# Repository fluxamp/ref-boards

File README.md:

## About

This repository contains the layout for two voltage reference boards intended as standalone devices and for integration with other modules.

Feel free to copy, modify and redistribute the schematic and layout.

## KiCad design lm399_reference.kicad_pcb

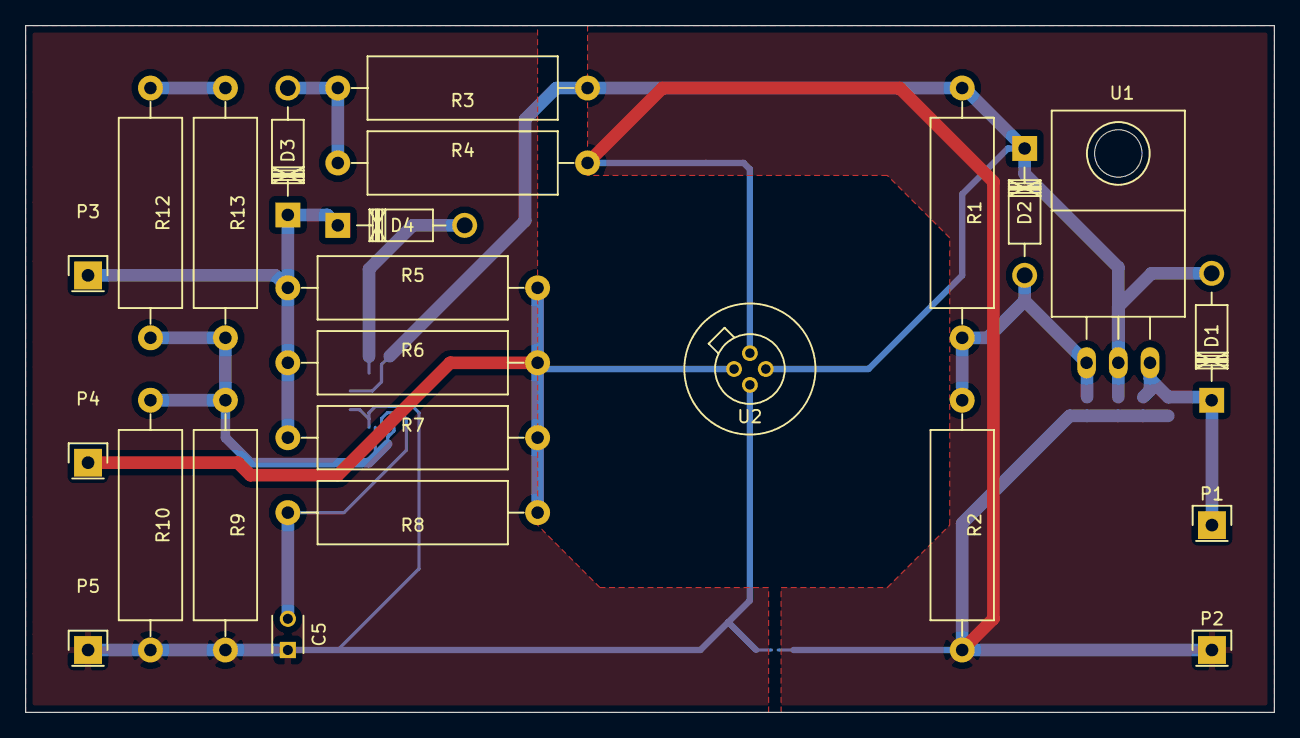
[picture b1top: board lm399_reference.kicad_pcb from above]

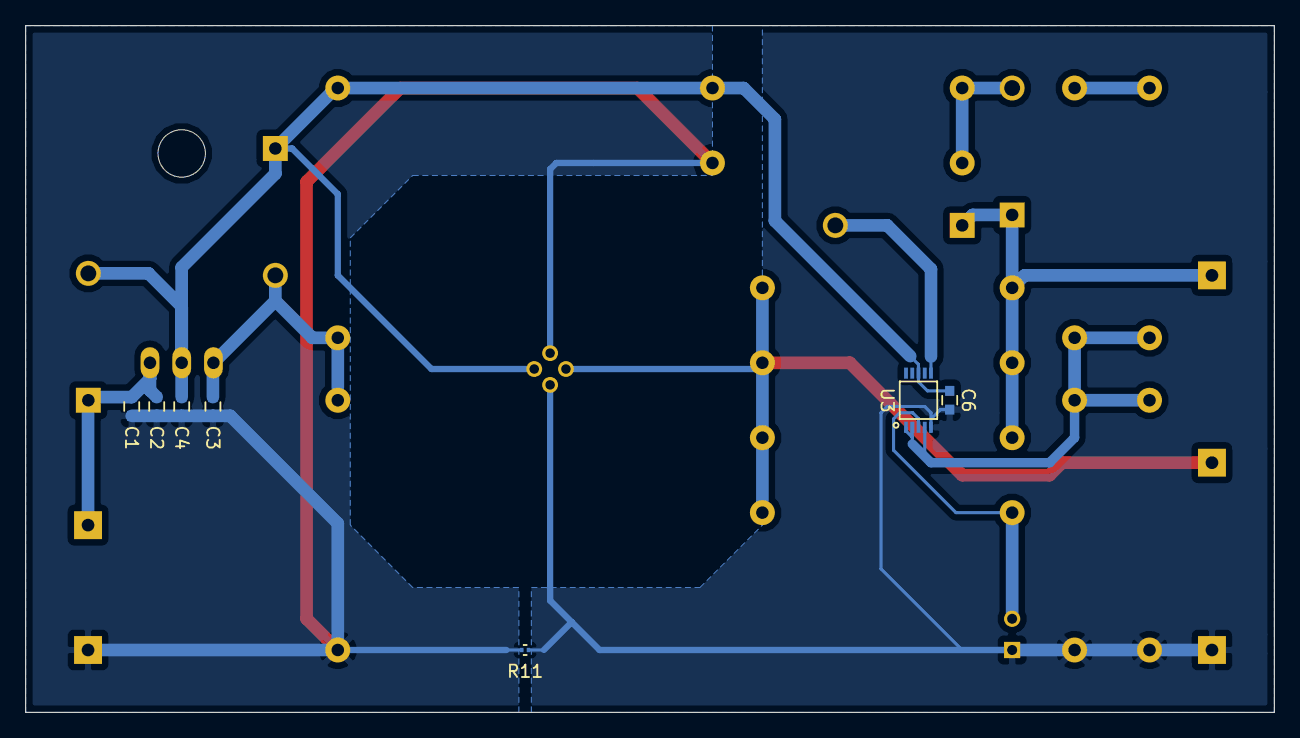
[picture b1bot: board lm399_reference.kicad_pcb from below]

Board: 2 copper layers, 100.0 x 55.0 mm, 31 parts (7 on the bottom side), 11 nets.

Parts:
C1, C3: 10u; C_0603
C2, C6: 100n; C_0603
C4: 1u; C_0603
C5: 100n; C_Disc_D3_P2.5
D1, D2: 1N4001; Diode_DO-41_SOD81_Horizontal_RM10
D3, D4: 1N4148; Diode_DO-41_SOD81_Horizontal_RM10
P1: VIN; Pin_Header_Straight_1x01
P2: GND; Pin_Header_Straight_1x01
P3: 10V; Pin_Header_Straight_1x01
P4: 7V; Pin_Header_Straight_1x01
P5: 10V_GND; Pin_Header_Straight_1x01
R1: 205R; Resistor_Horizontal_RM20mm
R2: 2k26; Resistor_Horizontal_RM20mm
R3, R9: 20k; Resistor_Horizontal_RM20mm
R4: 5k; Resistor_Horizontal_RM20mm
R5, R6, R7, R12, R13: 10k; Resistor_Horizontal_RM20mm
R8: 550R; Resistor_Horizontal_RM20mm
R10: 24k9; Resistor_Horizontal_RM20mm
R11: 0R; C_0201
U1: LM317T; TO-220
U2: LM399
U3: LTC2057-MS10; MSOP-10

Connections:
7V: P4.1, R5.2, R6.2, R7.2, R8.1, U2.1
+15V: C4.1, C6.1, D1.2, D2.1, R1.1, R3.1, U1.2, U2.3, U3.8
GND: C1.2, C2.2, C3.2, C4.2, P2.1, R2.2, R4.2, R11.2, U2.4
GNDA: C5.1, C6.2, P5.1, R9.2, R10.2, R11.1, U2.2, U3.5
unnamed: C3.1, D2.2, R1.2, R2.1, U1.1
unnamed: C5.2, R8.2, U3.3
unnamed: D3.1, D4.1, P3.1, R5.1, R6.1, R7.1, R12.1, R13.1
unnamed: D3.2, R3.2, R4.1
unnamed: D4.2, U3.6
unnamed: R9.1, R10.1, R12.2, R13.2, U3.1, U3.2, U3.4
VCC: C1.1, C2.1, D1.1, P1.1, U1.3

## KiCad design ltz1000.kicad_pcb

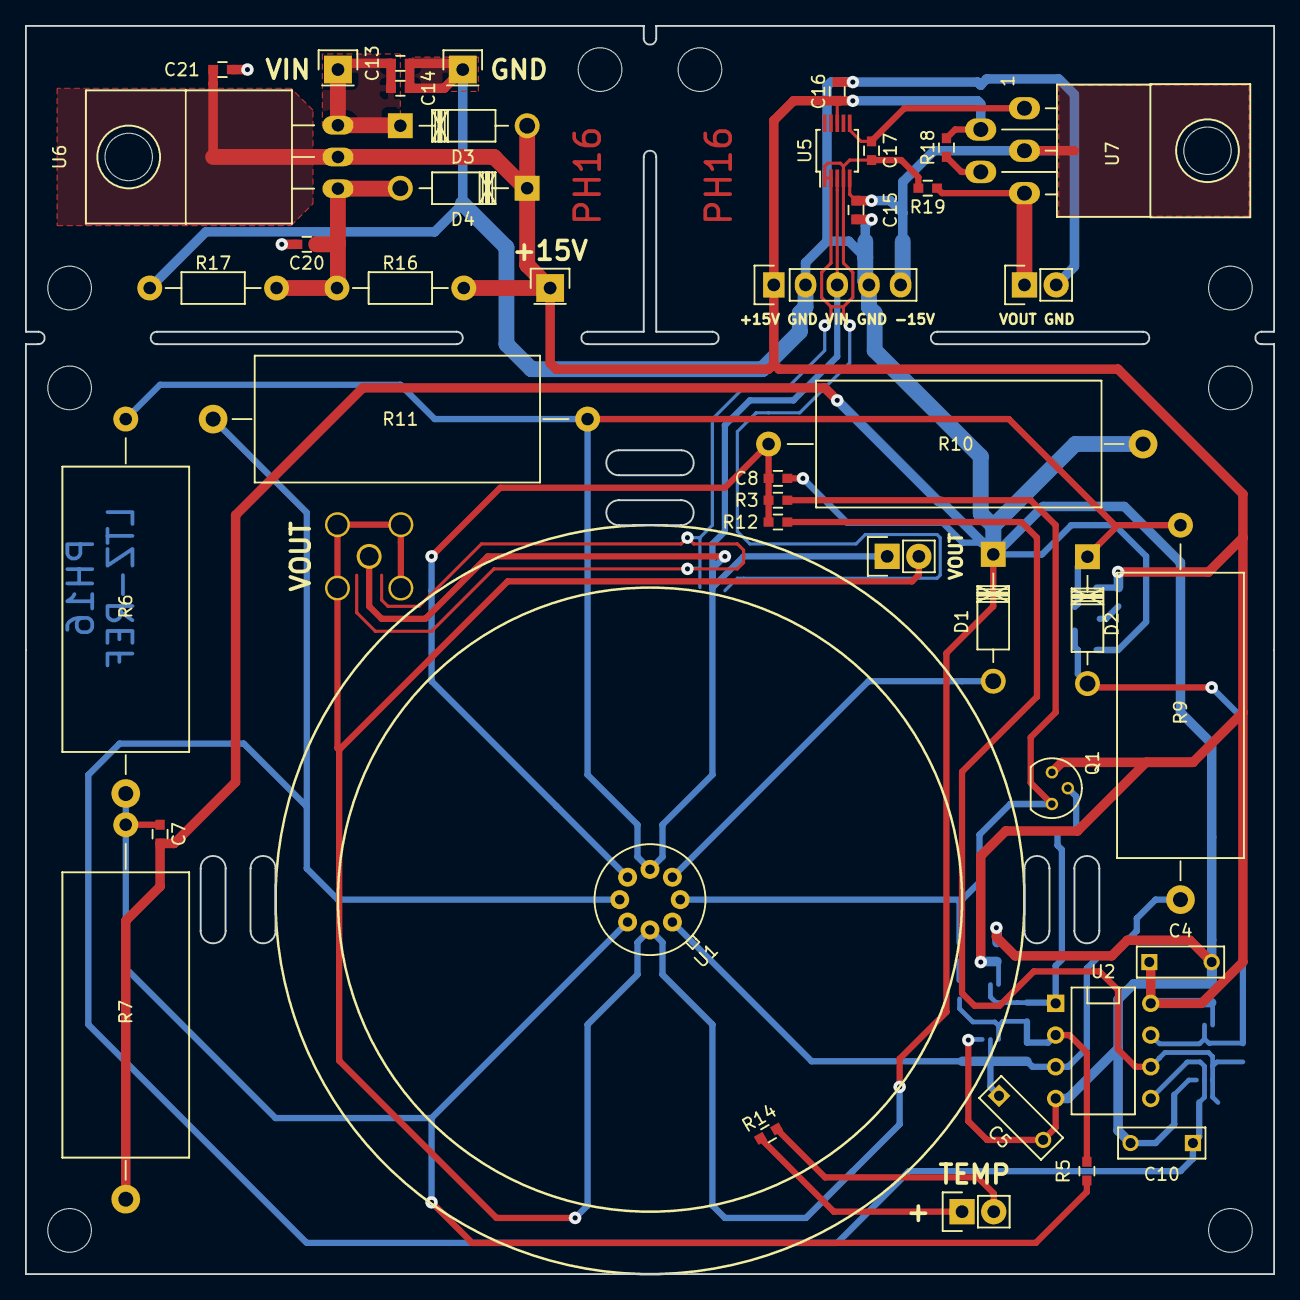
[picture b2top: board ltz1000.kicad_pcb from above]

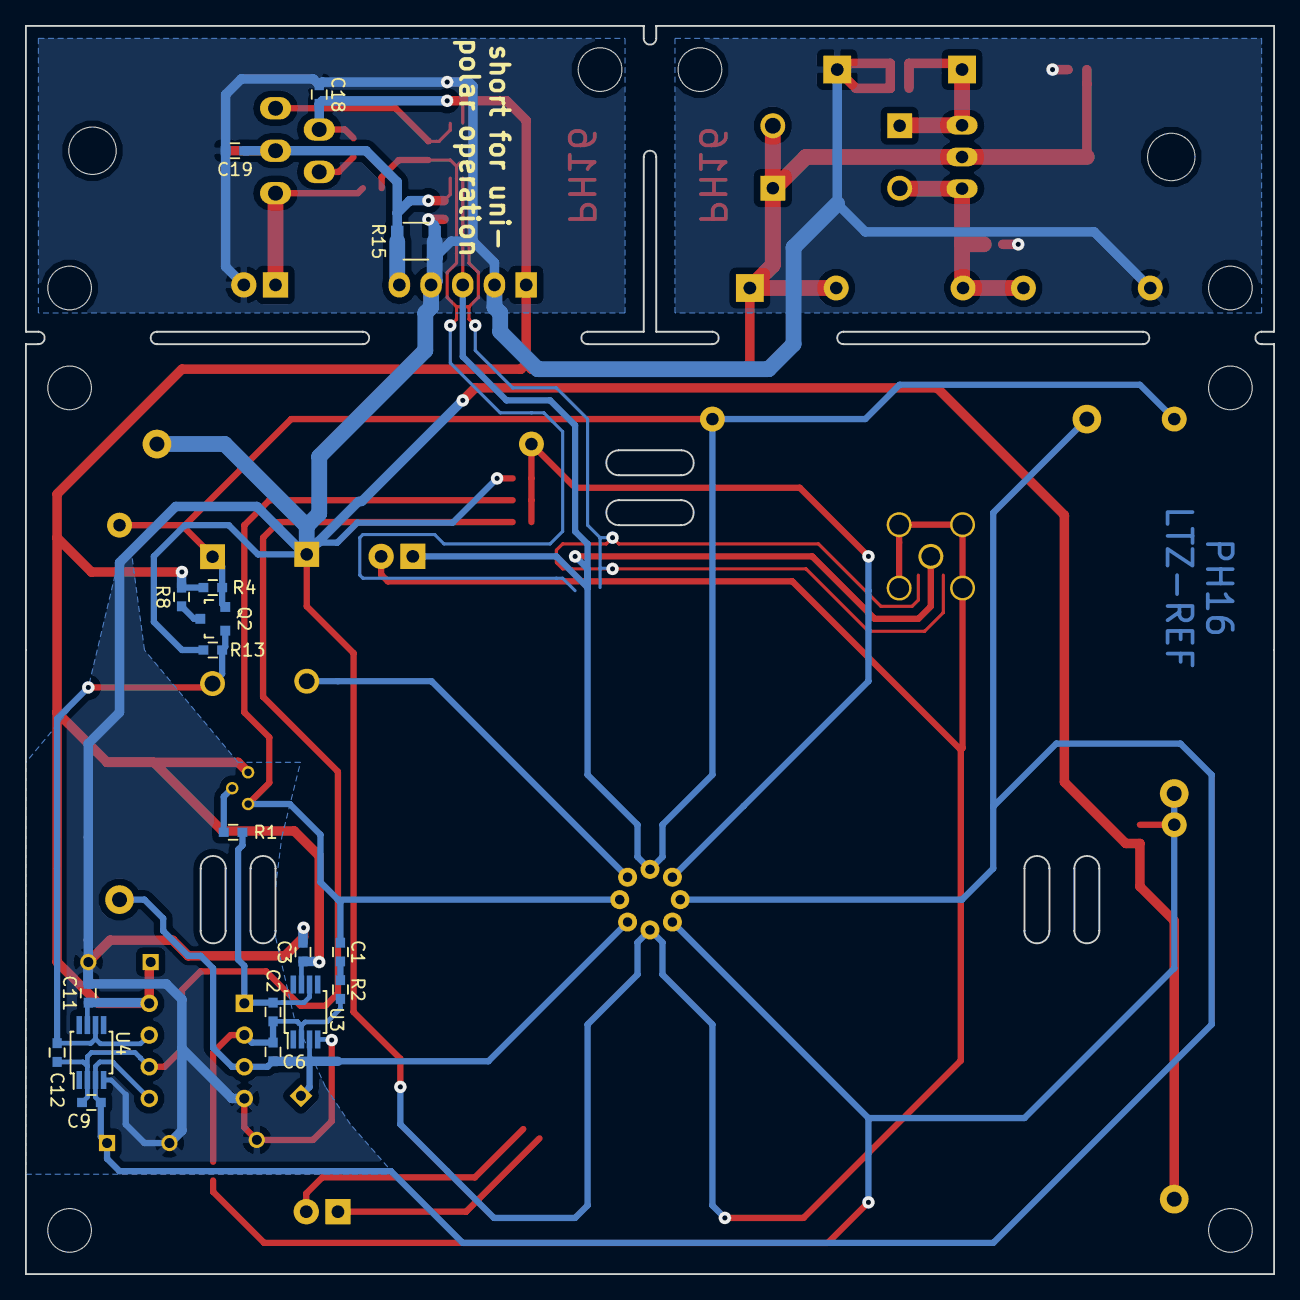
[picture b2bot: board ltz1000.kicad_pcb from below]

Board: 2 copper layers, 100.0 x 100.0 mm, 61 parts (18 on the bottom side), 25 nets.

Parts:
C1, C3, C11, C14, C15, C16, C17, C18, C19: 100n; C_0603
C2: 10n?; C_0603
C4, C5: 100n; C_Rect_L7_W2.5_P5
C6, C7, C8, C9, C12: 100n?; C_0603
C10: 22n; C_Rect_L7_W2.5_P5
C13, C20: 10u; C_0603
C21: 1u; C_0603
D1: 1N4148; Diode_DO-41_SOD81_Horizontal_RM10
D2: 1N4148?; Diode_DO-41_SOD81_Horizontal_RM10
D3, D4: 1N4001; Diode_DO-41_SOD81_Horizontal_RM10
P1, P2, P7: CONN_01X02; Pin_Header_Straight_1x02
P3: CONN_01X05; Pin_Header_Straight_1x05
P4, P5, P6: CONN_01X01; Pin_Header_Straight_1x01
P99: SMA
Q1: 2N3904; TO-92_Molded_Narrow
Q2: 2n7002; SOT-23
R1: 1k; C_0603
R2: 1M; C_0603
R3: 400k; C_0603
R4, R13: 1M?; C_0603
R5, R19: 10k; C_0603
R6: 12k500; Resistor_Horizontal_RM30mm
R7: 1k000; Resistor_Horizontal_RM30mm
R8: 100R?; C_0603
R9, R11: 70k000; Resistor_Horizontal_RM30mm
R10: 120R00; Resistor_Horizontal_RM30mm
R12: 10k?; C_0603
R14: RVAR; C_0603
R15: 0R; C_1210
R16: 205R; Resistor_Horizontal_RM10mm
R17: 2k26; Resistor_Horizontal_RM10mm
R18: R; C_0603
U1: LTZ1000; TO-5-8
U2: LT1013DN8; DIP-8__300
U3, U4: LTC2057-MS8; MSOP-8_3x3mm_Pitch0.65mm
U5: LTC2057-MS10; MSOP-10_3x3mm_Pitch0.5mm
U6: LM317T; TO-220_Neutral123_Horizontal
U7: LT1010CT; Pentawatt_Neutral_Staggered-Typ2_Horizontal_TO220-5-T05E

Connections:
+15V: C3.1, C4.1, C11.1, C16.1, C18.1, C21.1, D3.2, D4.1, P3.1, P6.1, Q1.1, R4.2, R8.1, R16.1, R18.1, U2.8, U3.7, U4.7, U5.8, U6.2, U7.2
-15V: C15.1, C19.1, P3.5, R15.2, U5.5, U7.3
GND: C3.2, C4.2, C5.2, C7.1, C8.1, C10.2, C11.2, C13.2, C14.2, C15.2, C16.2, C18.2, C19.2, C20.2, C21.2, D1.1, P2.2, P3.2, P3.4, P4.1, P7.2, P99.2, R7.2, R10.2, R13.2, R15.1, R17.2, U1.7, U2.4, U3.4, U4.4
unnamed: C1.1, Q1.3, R3.2, U1.1
unnamed: C1.2, R2.1
unnamed: C2.1, R1.1, U2.1, U3.6
unnamed: C2.2, C6.2, R2.2, R5.2, U2.2, U3.2
unnamed: C5.1, C6.1, R9.2, U1.8, U2.3, U3.3
unnamed: C7.2, R5.1, R6.2, R7.1, U1.6
unnamed: C8.2, R3.1, R10.1, R12.2, U1.4
unnamed: C9.2, C10.1, R11.2, U1.5, U2.5, U4.3
unnamed: C12.1, D2.2, Q2.1, R13.1, U2.7, U4.6
unnamed: C9.1, C12.2, R12.1, U2.6, U4.2
unnamed: C17.1, U5.6, U7.1
unnamed: C17.2, R19.2, U5.1, U5.2, U5.4
unnamed: C20.1, D4.2, R16.2, R17.1, U6.1
unnamed: D1.2, U1.2
unnamed: P7.1, R19.1, U7.5
unnamed: Q1.2, R1.2
unnamed: Q2.3, R8.2
unnamed: R18.2, U7.4
TEMP+: P1.1, R14.1
TEMP-: P1.2, R14.2
VIN: C13.1, C14.1, D3.1, P5.1, U6.3
VREF+: D2.1, P2.1, P3.3, P99.1, Q2.2, R4.1, R6.1, R9.1, R11.1, U1.3, U5.3

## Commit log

2017-11-05 added board files
